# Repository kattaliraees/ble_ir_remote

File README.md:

# IR Remote with BLE interface and App 
IR remote with BLE interface - Under development

- [x] Hardware
- [x] Firmware
- [ ] Mobile App

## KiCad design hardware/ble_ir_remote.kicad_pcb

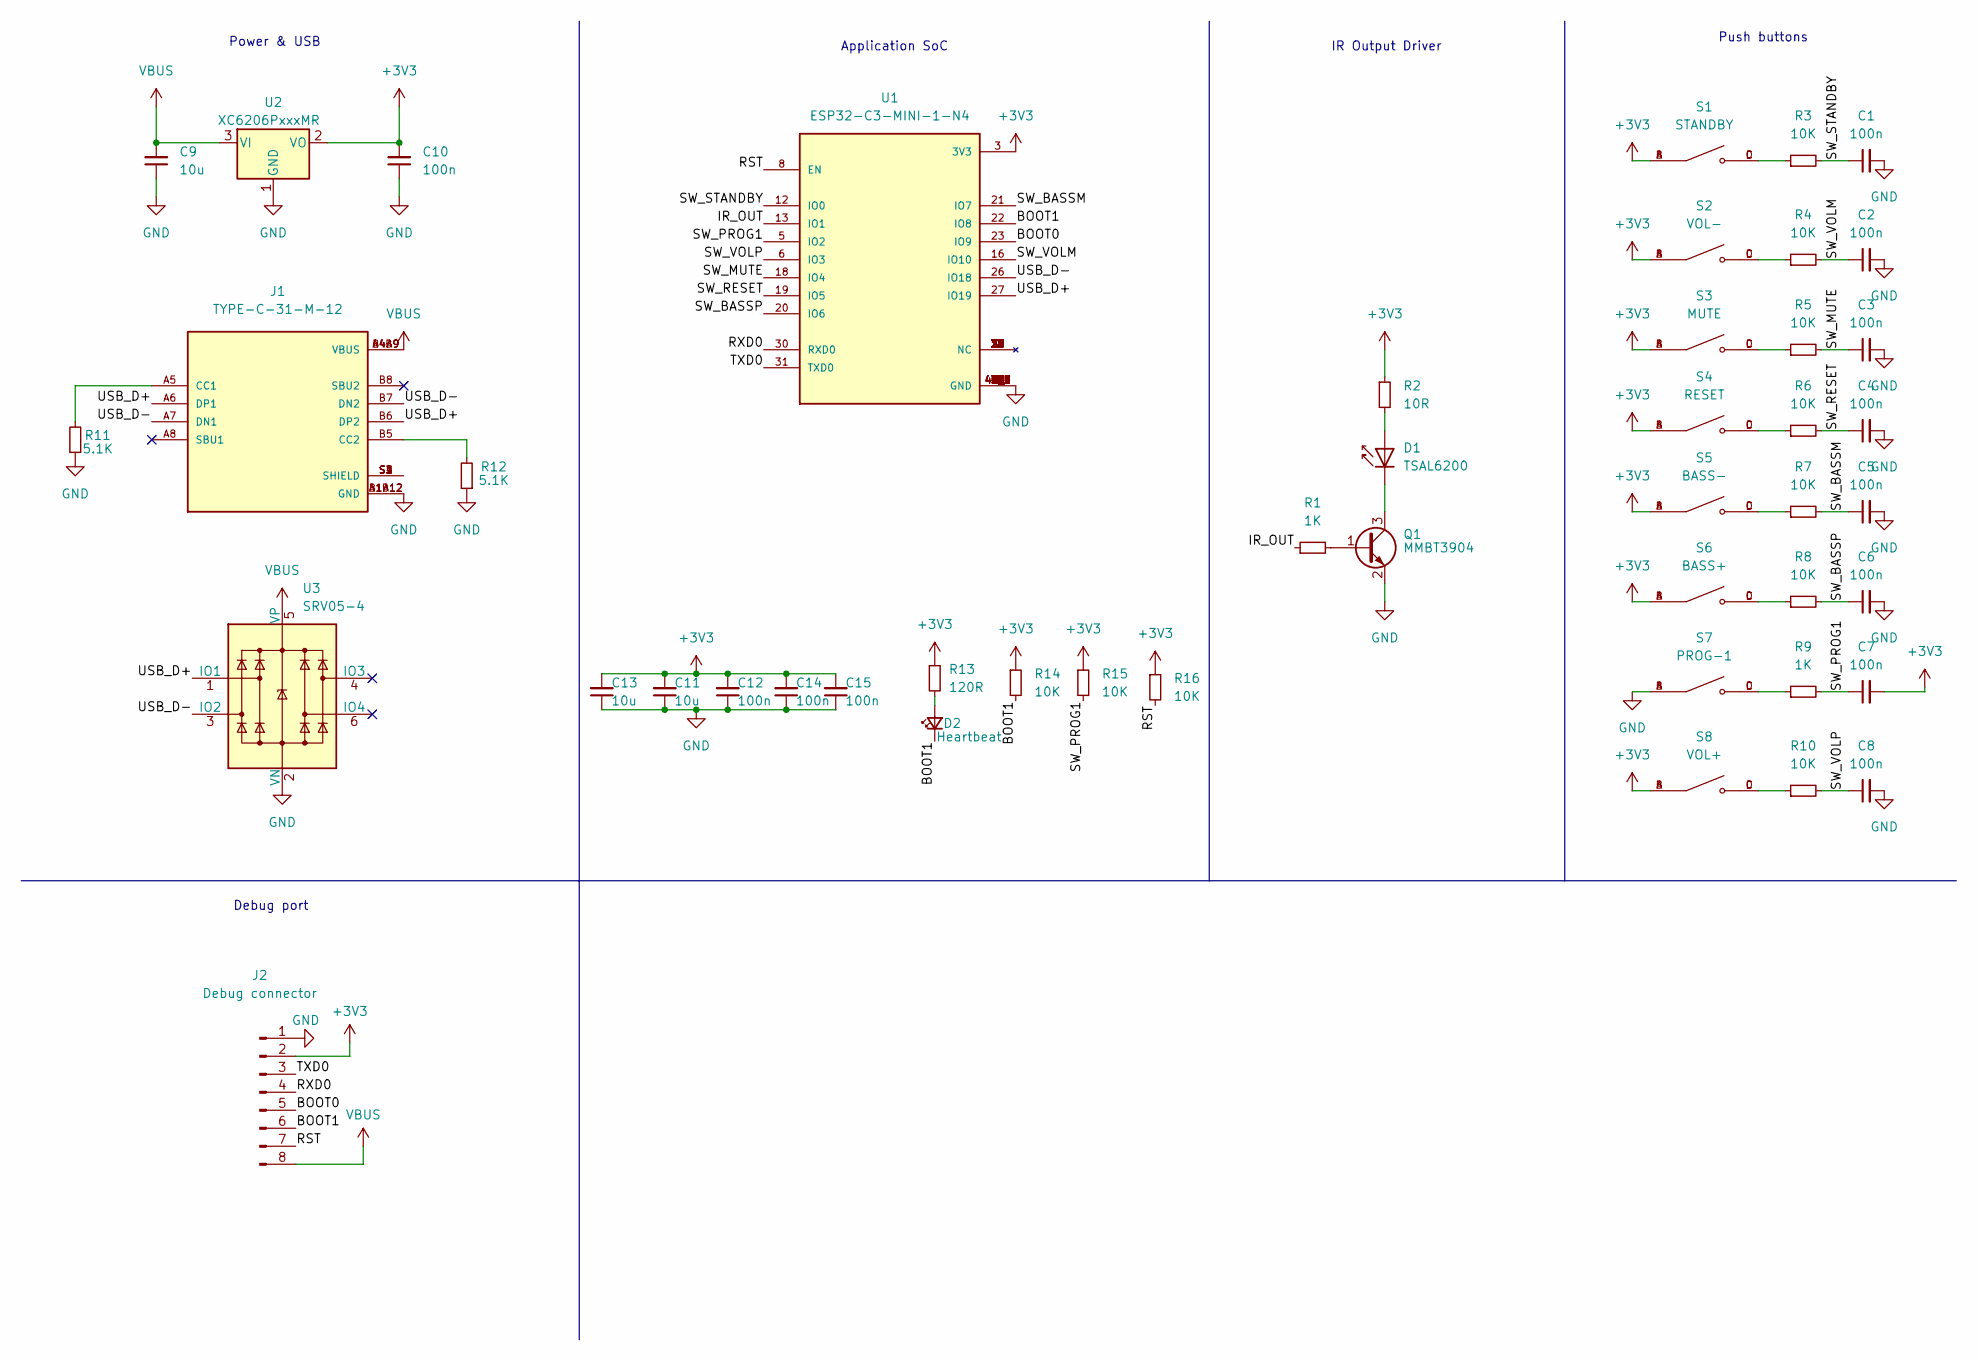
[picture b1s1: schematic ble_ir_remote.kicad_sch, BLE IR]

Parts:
C1, C2, C3, C4, C5, C6, C7, C8, C10, C12, C14, C15: 100n; C_0603_1608Metric
C9, C11, C13: 10u; C_0603_1608Metric
D1: TSAL6200; LED_D3.0mm_IRBlack
D2: Heartbeat; LED_0603_1608Metric
J1: TYPE-C-31-M-12; HRO_TYPE-C-31-M-12; PARTREV A
J2: Debug connector; PinHeader_1x08_P2.54mm_Vertical
Q1: MMBT3904; SOT-23
R1, R9: 1K; R_0603_1608Metric
R2: 10R; R_0603_1608Metric
R3, R4, R5, R6, R7, R8, R10, R14, R15, R16: 10K; R_0603_1608Metric
R11, R12: 5.1K; R_0603_1608Metric
R13: 120R; R_0603_1608Metric
S1: STANDBY; SW_TS-1187A-B-A-B; PARTREV A0
S2: VOL-; SW_TS-1187A-B-A-B; PARTREV A0
S3: MUTE; SW_TS-1187A-B-A-B; PARTREV A0
S4: RESET; SW_TS-1187A-B-A-B; PARTREV A0
S5: BASS-; SW_TS-1187A-B-A-B; PARTREV A0
S6: BASS+; SW_TS-1187A-B-A-B; PARTREV A0
S7: PROG-1; SW_TS-1187A-B-A-B; PARTREV A0
S8: VOL+; SW_TS-1187A-B-A-B; PARTREV A0
U1: ESP32-C3-MINI-1-N4; XCVR_ESP32-C3-MINI-1-N4; PARTREV v1.0
U2: XC6206PxxxMR; SOT-23
U3: SRV05-4; SOT-23-6

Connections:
+3V3: C7.2, C10.2, C11.2, C12.2, C13.2, C14.2, C15.2, J2.2, R2.1, R13.1, R14.1, R15.1, R16.1, S1.A, S1.B, S2.A, S2.B, S3.A, S3.B, S4.A, S4.B, S5.A, S5.B, S6.A, S6.B, S8.A, S8.B, U1.3 (3V3), U2.2 (VO)
/BOOT0: J2.5, U1.23 (IO9)
/BOOT1: D2.1 (K), J2.6, R14.2, U1.22 (IO8)
/IR_OUT: R1.1, U1.13 (IO1)
/RST: J2.7, R16.2, U1.8 (EN)
/RXD0: J2.4, U1.30 (RXD0)
/SW_BASSM: C5.1, R7.2, U1.21 (IO7)
/SW_BASSP: C6.1, R8.2, U1.20 (IO6)
/SW_MUTE: C3.1, R5.2, U1.18 (IO4)
/SW_PROG1: C7.1, R9.2, R15.2, U1.5 (IO2)
/SW_RESET: C4.1, R6.2, U1.19 (IO5)
/SW_STANDBY: C1.1, R3.2, U1.12 (IO0)
/SW_VOLM: C2.1, R4.2, U1.16 (IO10)
/SW_VOLP: C8.1, R10.2, U1.6 (IO3)
/TXD0: J2.3, U1.31 (TXD0)
/USB_D+: J1.A6 (DP1), J1.B6 (DP2), U1.27 (IO19), U3.1 (IO1)
/USB_D-: J1.A7 (DN1), J1.B7 (DN2), U1.26 (IO18), U3.3 (IO2)
GND: C1.2, C2.2, C3.2, C4.2, C5.2, C6.2, C8.2, C9.1, C10.1, C11.1, C12.1, C13.1, C14.1, C15.1, J1.A1B12 (GND), J1.B1A12 (GND), J2.1, Q1.2 (E), R11.1, R12.1, S7.A, S7.B, U1.1 (GND), U1.2 (GND), U1.11 (GND), U1.14 (GND), U1.36 (GND), U1.37 (GND), U1.38 (GND), U1.39 (GND), U1.40 (GND), U1.41 (GND), U1.42 (GND), U1.43 (GND), U1.44 (GND), U1.45 (GND), U1.46 (GND), U1.47 (GND), U1.48 (GND), U1.49_1 (GND), U1.49_2 (GND), U1.49_3 (GND), U1.49_4 (GND), U1.49_5 (GND), U1.49_6 (GND), U1.49_7 (GND), U1.49_8 (GND), U1.49_9 (GND), U1.50 (GND), U1.51 (GND), U1.52 (GND), U1.53 (GND), U2.1 (GND), U3.2 (VN)
unnamed: D1.1 (K), Q1.3 (C)
unnamed: D2.2 (A), R13.2
unnamed: J1.A5 (CC1), R11.2
unnamed: J1.B5 (CC2), R12.2
unnamed: J1.S1 (SHIELD), J1.S2 (SHIELD), J1.S3 (SHIELD), J1.S4 (SHIELD)
unnamed: Q1.1 (B), R1.2
unnamed: D1.2 (A), R2.2
unnamed: R3.1, S1.C, S1.D
unnamed: R4.1, S2.C, S2.D
unnamed: R5.1, S3.C, S3.D
unnamed: R6.1, S4.C, S4.D
unnamed: R7.1, S5.C, S5.D
unnamed: R8.1, S6.C, S6.D
unnamed: R9.1, S7.C, S7.D
unnamed: R10.1, S8.C, S8.D
VBUS: C9.2, J1.A4B9 (VBUS), J1.B4A9 (VBUS), J2.8, U2.3 (VI), U3.5 (VP)

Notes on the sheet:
Application SoC
Power & USB
Debug port
Push buttons
IR Output Driver

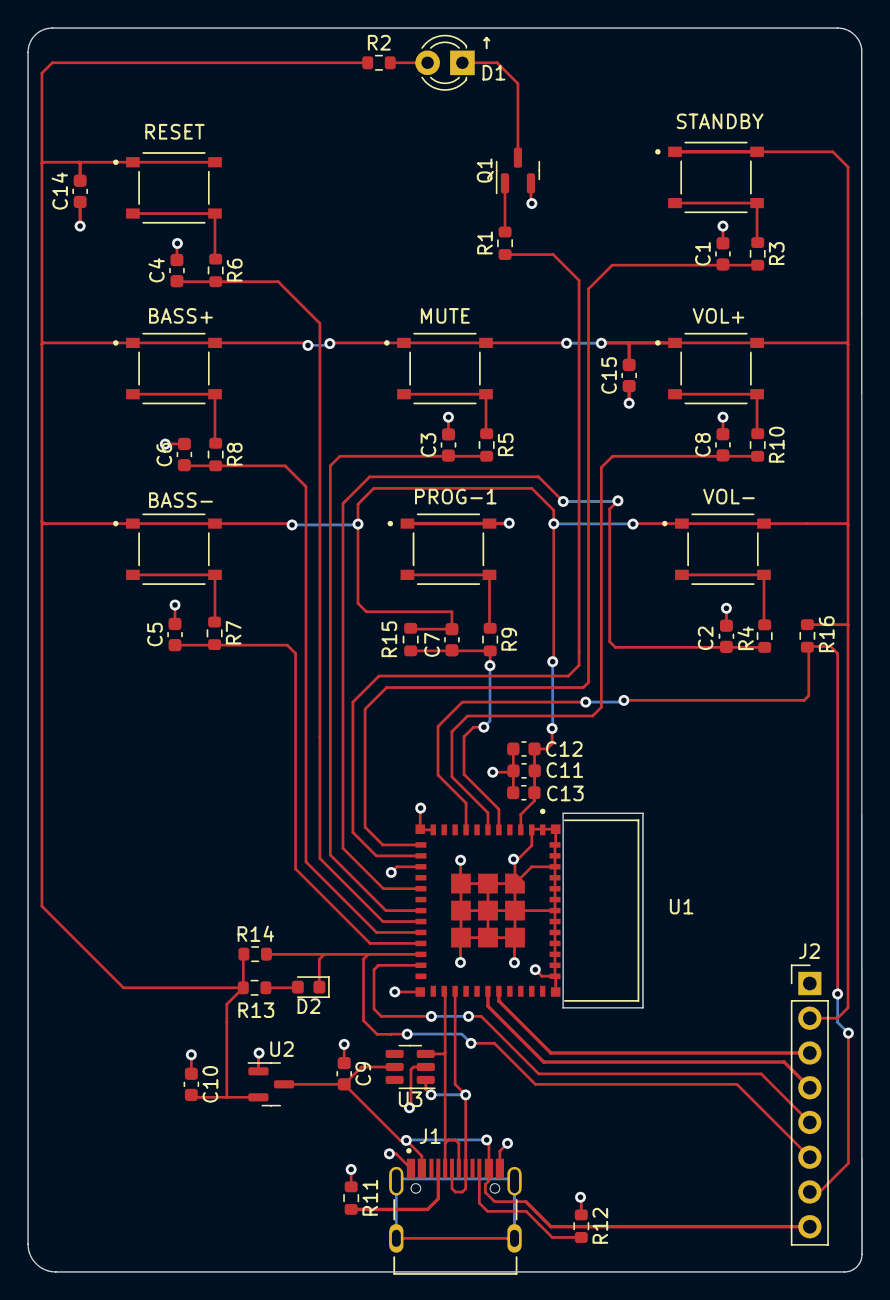
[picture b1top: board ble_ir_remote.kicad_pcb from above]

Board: 2 copper layers, 61.0 x 90.9 mm, 47 parts (0 on the bottom side), 34 nets.

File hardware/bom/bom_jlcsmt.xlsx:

Comment | Designator | Footprint | JLCPCB Part #（optional）
100nF | C1, C2, C3, C4, C5, C6, C7, C8, C10, C12, C14, C15 | C_0603 | C14663
10uF | C9, C11, C13 | C_0603 | C19702
10K | R3, R4, R5, R6, R7, R8, R10, R14, R15, R16 | R_0603 | C25804
5.1K | R11, R12 | R_0603 | C23186
1K | R1, R9 | R_0603 | C23241
10R | R2 | R_0603 | C22859
120R | R13 | R_0603 | C22787
TSAL6200 (Right angle) | D1 | LED-TH_BD5.0-P2.54-FD | C55528
Red LED | D2 | LED_0603 | C2286
ESP32-C3-MINI-1-N4 | U1 | SMD,13.2x16.6x2.4mm | C2838502
XC6206P332MR | U2 | SOT-23-3L | C5446
SRV05-4-P-T7 | U3 | SOT-23-6L | C85364
MMBT3904 | Q1 | SOT-23-3 | C20526
TS-1187A-B | S1 | SMD-SW-4_5.1x5.1x1.5 | C318884
TS-1187A-B | S2 | SMD-SW-4_5.1x5.1x1.5 | C318884
TS-1187A-B | S3 | SMD-SW-4_5.1x5.1x1.5 | C318884
TS-1187A-B | S4 | SMD-SW-4_5.1x5.1x1.5 | C318884
TS-1187A-B | S5 | SMD-SW-4_5.1x5.1x1.5 | C318884
TS-1187A-B | S6 | SMD-SW-4_5.1x5.1x1.5 | C318884
TS-1187A-B | S7 | SMD-SW-4_5.1x5.1x1.5 | C318884
TS-1187A-B | S8 | SMD-SW-4_5.1x5.1x1.5 | C318884
TYPE-C-31-M-12 | J1 | TYPE-C-31_L8.94_W7.3 | C165948

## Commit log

2022-05-15 gitignore
2022-05-15 kicad proj
2022-05-15 aded .lib files
2022-05-16 lib files re-added
2022-05-16 sch progress
2022-05-16 usb conn added
2022-05-16 sch prgrs
2022-05-17 sch prgs
2022-05-17 step file mapped
2022-05-21 basic placement
2022-05-21 routing
2022-05-22 fine tuning
2022-05-23 cleanup
2022-05-24 firmware set-target esp32c3
2022-05-25 fixes
2022-05-26 final gerber
2022-06-10 basic hardware test
2022-06-10 idf v5 compatible
2022-06-11 ir lib added
2022-06-20 app progress
2022-06-26 prgrs
2022-07-09 removing unsupported flutter targets
2022-07-09 android target added
2022-07-09 ble libs added
2022-07-09 vsocde c/cpp config
2022-07-09 ble preiph only mode
2022-07-09 ir testing
2022-07-10 idf 5
2022-07-12 Updated value for standby
2022-07-12 test code
2022-07-12 log cleanup
2022-07-12 4mb flash
